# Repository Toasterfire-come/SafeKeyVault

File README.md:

# SafeKeyVault

This project is designed to be a copmplete and total alternative to managed password holders. Including features  like one click copy for authenticators which allows the same access as a microsoft auth, but with more controll. Additionaly features like autofill, and hardware key capabilities are all wrapped in the same authenticator. There is one universal settings and interface (HTML) to allow for any device with a browser to open and use passwords. This board was desiged as complete alternative to web extentions or websites having a data breach and you loosing all of your passwords. Features to prevent this are the Phishing noteices where when you attempt to fill in your password or use the device on a site like G00gle.com instead of google.com, a popup will appear informing you of a potential scam. As well as autogenerated secure passwords, week password indicators, and very good cryptography. This device uses a locked to pin system and ATECC608A binding points. With more updates to come. I built this project because I was tired of Google asking me to save every password and wanted a local opensource alternitive that does it all.

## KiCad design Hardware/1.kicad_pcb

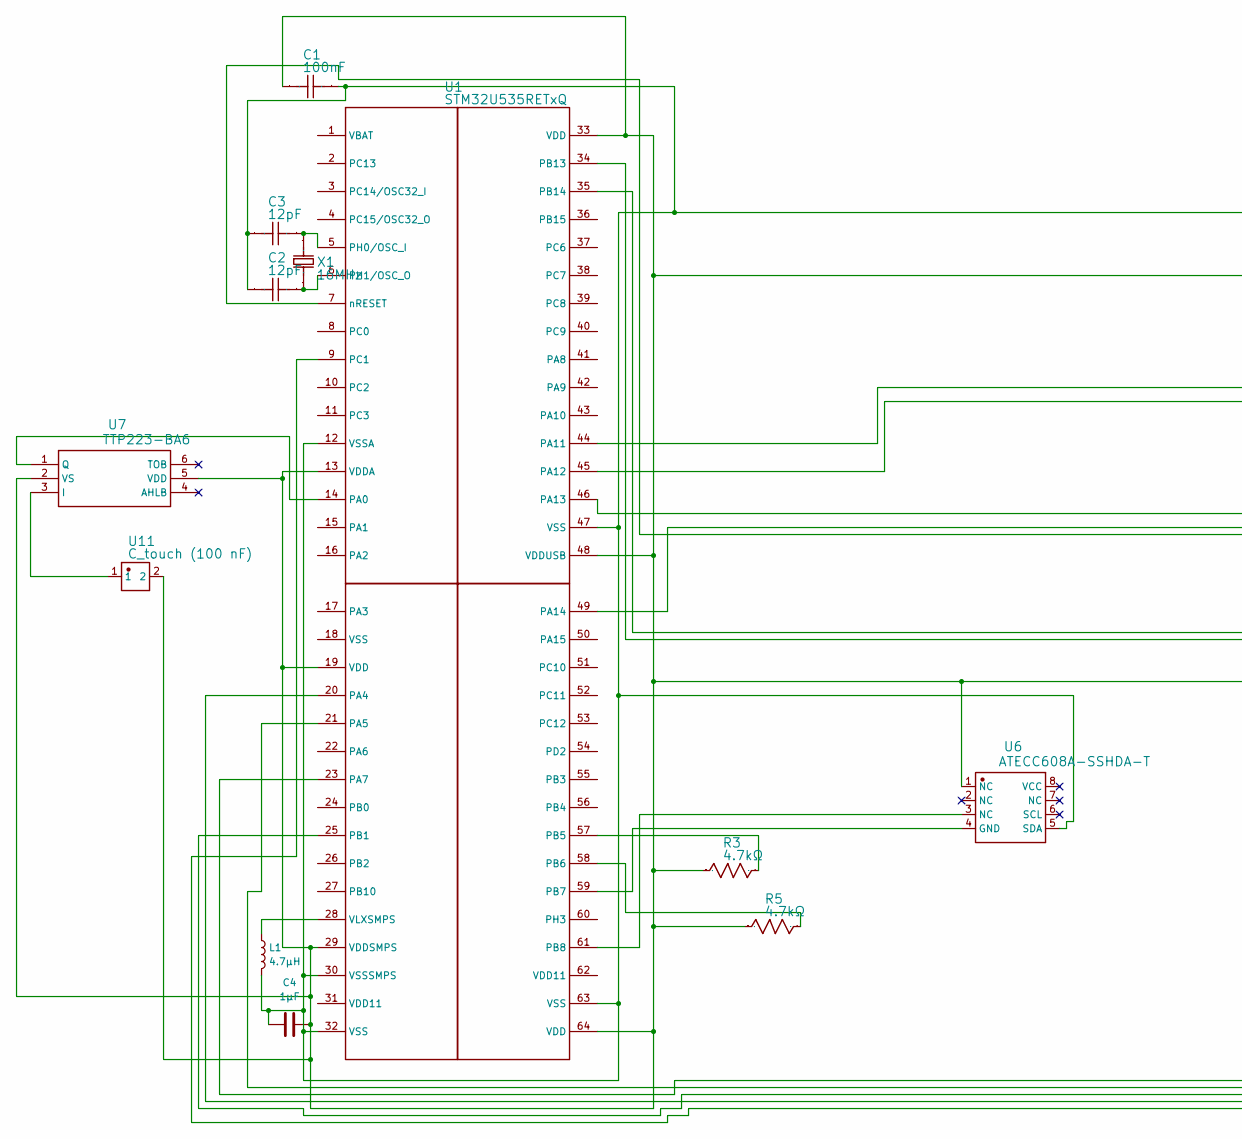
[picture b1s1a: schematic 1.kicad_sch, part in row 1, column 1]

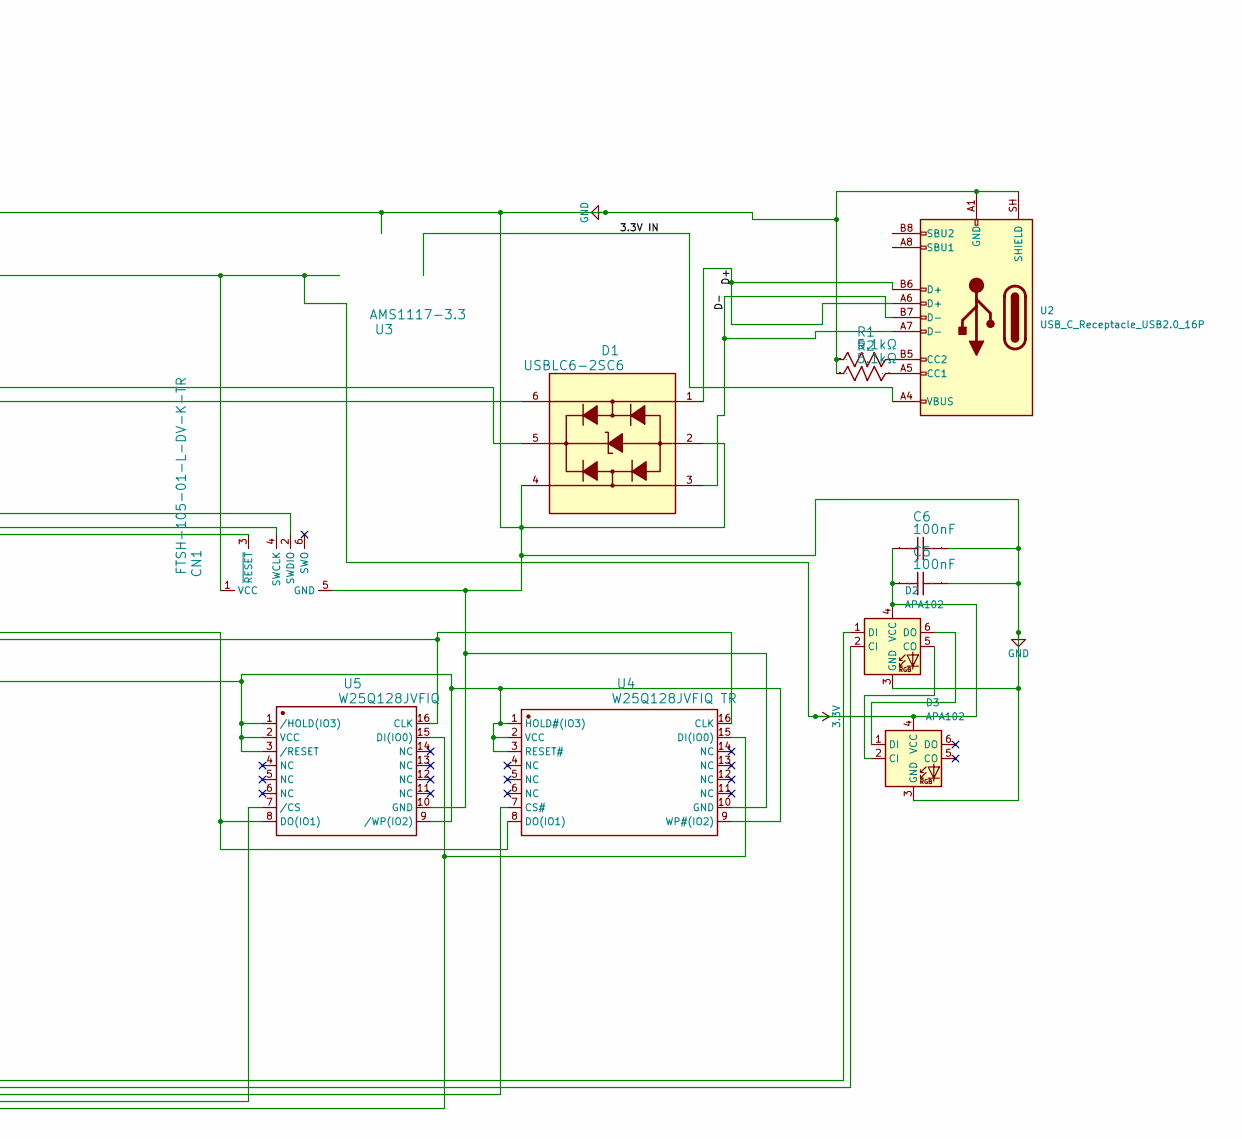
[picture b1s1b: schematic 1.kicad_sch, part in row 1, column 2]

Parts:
C1, C5, C6: 100nF; C_0603_1608Metric
C2, C3: 12pF; C_0603_1608Metric
C4: 1µF; C_0603_1608Metric
CN1: FTSH-105-01-L-DV-K-TR; Tag-Connect_TC2030-IDC-NL_2x03_P1.27mm_Vertical; Manufacturer Part FTSH-105-01-L-DV-K-TR
D1: USBLC6-2SC6; SOT-23-6; Manufacturer Part USBLC6-2SC6
D2, D3: APA102; LED-APA102-2020
L1: 4.7µH; L_0603_1608Metric
R1, R2: 5.1kΩ; R_0603_1608Metric
R3, R5: 4.7kΩ; R_0603_1608Metric
U1: STM32U535RETxQ; LQFP-64_10x10mm_P0.5mm
U2: USB_C_Receptacle_USB2.0_16P; USB_C_Receptacle_GCT_USB4105-xx-A_16P_TopMnt_Horizontal
U3: AMS1117-3.3; SOT-223-3_TabPin2; Manufacturer Part AMS1117-3.3
U4: W25Q128JVFIQ TR; SOIC-16_3.9x9.9mm_P1.27mm; Manufacturer Part W25Q128JVFIQ TR
U5: W25Q128JVFIQ; SOIC-16_3.9x9.9mm_P1.27mm; Manufacturer Part W25Q128JVFIQ
U6: ATECC608A-SSHDA-T; SOT-23-8; Manufacturer Part ATECC608A-SSHDA-T
U7: TTP223-BA6; SOT-23-6; Manufacturer Part TTP223-BA6
U11: C_touch (100 nF); C_0603_1608Metric; Manufacturer Part TOUCH
X1: 16MHz; Crystal_SMD_3225-4Pin_3.2x2.5mm; Manufacturer Part NX3225GB-16MHZ-STD-CRA-2

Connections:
3.3V: C1.1, C4.1, C5.1, C6.1, CN1.1 (VCC), D2.4 (VCC), D3.4 (VCC), R3.1, R5.1, U1.13 (VDDA), U1.19 (VDD), U1.29 (VDDSMPS), U1.33 (VDD), U1.48 (VDDUSB), U1.64 (VDD), U3.2 (VO), U4.1 (HOLD#(IO3)), U4.2 (VCC), U4.3 (RESET#), U4.9 (WP#(IO2)), U5.1 (/HOLD(IO3)), U5.2 (VCC), U5.3 (/RESET), U5.9 (/WP(IO2)), U6.1 (NC), U7.2 (VS), U7.5 (VDD), U11.2; also elsewhere on the board
/3.3V IN: U3.3 (VI); also elsewhere on the board
/D+: D1.1, U2.A6 (D+), U2.B6 (D+); also elsewhere on the board
/D-: D1.3, U2.A7 (D-), U2.B7 (D-); also elsewhere on the board
GND: C1.2, C2.1, C3.1, C4.2, C5.2, C6.2, CN1.5 (GND), D1.2, D1.4, D2.3 (GND), D3.3 (GND), L1.2, R1.1, R2.1, U1.12 (VSSA), U1.30 (VSSSMPS), U1.32 (VSS), U1.47 (VSS), U1.63 (VSS), U2.A1 (GND), U2.A12 (GND), U2.B1 (GND), U2.B12 (GND), U2.SH (SHIELD), U3.1 (GND), U4.10 (GND), U5.10 (GND), U6.5 (SDA); also elsewhere on the board
unnamed 5: CN1.4 (SWCLK), U1.49 (PA14); also elsewhere on the board
unnamed 6: CN1.2 (SWDIO), U1.46 (PA13); also elsewhere on the board
unnamed 7: CN1.3 (~RESET), U1.7 (nRESET); also elsewhere on the board
unnamed 8: D2.2 (CI), U1.21 (PA5); also elsewhere on the board
unnamed: D2.5 (CO), D3.2 (CI)
unnamed 10: D2.1 (DI), U1.23 (PA7); also elsewhere on the board
unnamed: D2.6 (DO), D3.1 (DI)
unnamed 12: R2.2, U2.A5 (CC1); also elsewhere on the board
unnamed 13: R1.2, U2.B5 (CC2); also elsewhere on the board
unnamed 14: U1.14 (PA0), U7.1 (Q); also elsewhere on the board
unnamed 15: U1.20 (PA4), U5.7 (/CS); also elsewhere on the board
unnamed 16: D1.5, U1.44 (PA11); also elsewhere on the board
unnamed 17: D1.6, U1.45 (PA12); also elsewhere on the board
unnamed 18: U1.25 (PB1), U4.7 (CS#); also elsewhere on the board
unnamed 19: R3.2, U1.57 (PB5); also elsewhere on the board
unnamed 20: R5.2, U1.58 (PB6); also elsewhere on the board
unnamed 21: U1.59 (PB7), U6.4 (GND); also elsewhere on the board
unnamed 22: U1.61 (PB8), U6.3 (NC); also elsewhere on the board
unnamed 23: U1.34 (PB13), U4.16 (CLK), U5.16 (CLK); also elsewhere on the board
unnamed 24: U1.35 (PB14), U4.8 (DO(IO1)), U5.8 (DO(IO1)); also elsewhere on the board
unnamed 25: U1.9 (PC1), U4.15 (DI(IO0)), U5.15 (DI(IO0)); also elsewhere on the board
unnamed 26: C3.2, U1.5 (PH0/OSC_I), X1.2; also elsewhere on the board
unnamed 27: C2.2, U1.6 (PH1/OSC_O), X1.1; also elsewhere on the board
unnamed 28: L1.1, U1.28 (VLXSMPS); also elsewhere on the board
unnamed: U2.A4 (VBUS), U2.A9 (VBUS), U2.B4 (VBUS), U2.B9 (VBUS)
unnamed: U7.3 (I), U11.1

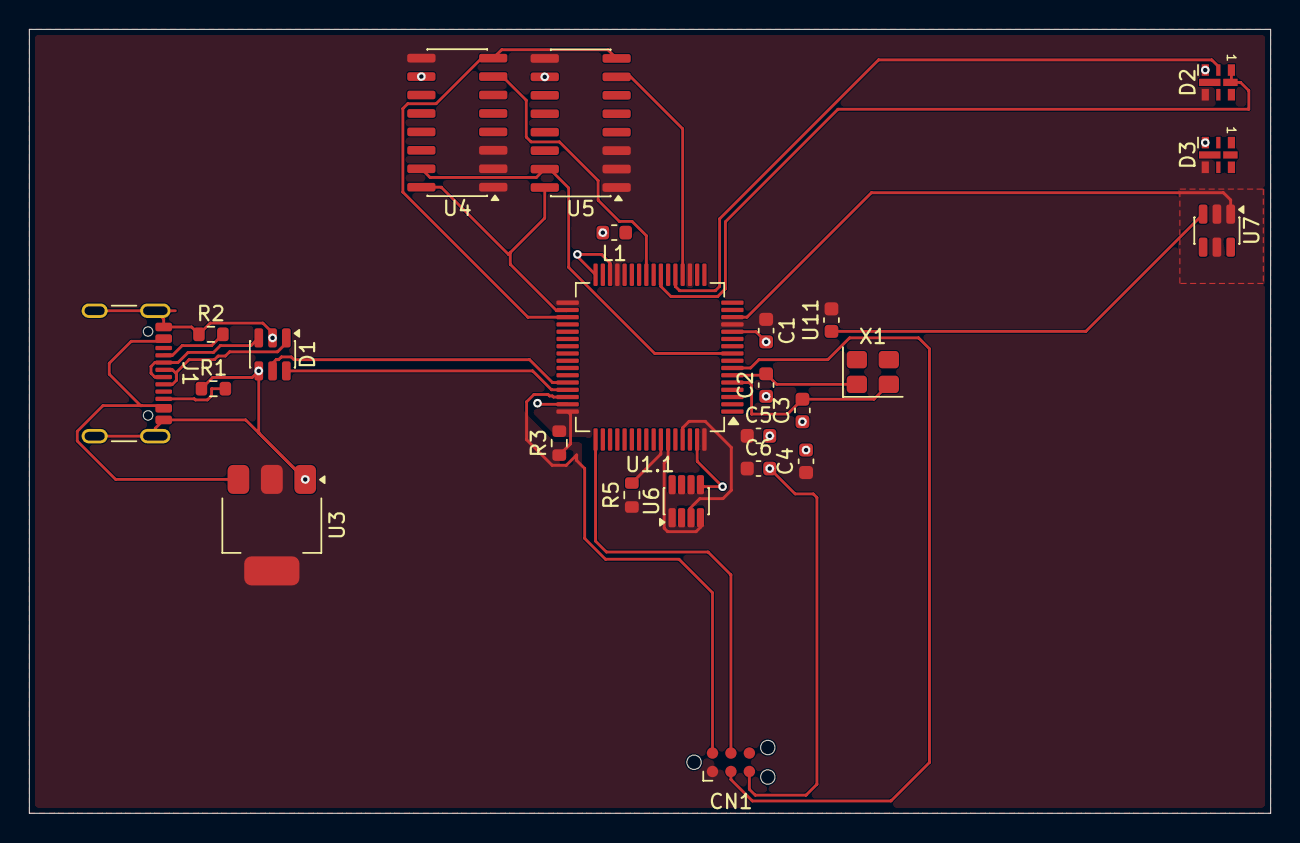
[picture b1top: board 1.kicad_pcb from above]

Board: 2 copper layers, 85.5 x 54.0 mm, 24 parts (0 on the bottom side), 30 nets.

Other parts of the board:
J1: USB_C_Receptacle_USB2.0_16P; USB_C_Receptacle_GCT_USB4105-xx-A_16P_TopMnt_Horizontal
U1.1: STM32U535RETxQ; LQFP-64_10x10mm_P0.5mm

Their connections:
3.3V: U1.1.13 (VDDA), U1.1.19 (VDD), U1.1.29 (VDDSMPS), U1.1.33 (VDD), U1.1.48 (VDDUSB), U1.1.64 (VDD); also elsewhere on the board
/3.3V IN: J1.A4 (VBUS), J1.A9 (VBUS), J1.B4 (VBUS), J1.B9 (VBUS); also elsewhere on the board
/D+: J1.A6 (D+), J1.B6 (D+); also elsewhere on the board
/D-: J1.A7 (D-), J1.B7 (D-); also elsewhere on the board
GND: J1.A1 (GND), J1.A12 (GND), J1.B1 (GND), J1.B12 (GND), J1.SH (SHIELD), U1.1.12 (VSSA), U1.1.30 (VSSSMPS), U1.1.32 (VSS), U1.1.47 (VSS), U1.1.63 (VSS); also elsewhere on the board
unnamed 5: U1.1.49 (PA14); also elsewhere on the board
unnamed 6: U1.1.46 (PA13); also elsewhere on the board
unnamed 7: U1.1.7 (nRESET); also elsewhere on the board
unnamed 8: U1.1.21 (PA5); also elsewhere on the board
unnamed 10: U1.1.23 (PA7); also elsewhere on the board
unnamed 12: J1.A5 (CC1); also elsewhere on the board
unnamed 13: J1.B5 (CC2); also elsewhere on the board
unnamed 14: U1.1.14 (PA0); also elsewhere on the board
unnamed 15: U1.1.20 (PA4); also elsewhere on the board
unnamed 16: U1.1.44 (PA11); also elsewhere on the board
unnamed 17: U1.1.45 (PA12); also elsewhere on the board
unnamed 18: U1.1.25 (PB1); also elsewhere on the board
unnamed 19: U1.1.57 (PB5); also elsewhere on the board
unnamed 20: U1.1.58 (PB6); also elsewhere on the board
unnamed 21: U1.1.59 (PB7); also elsewhere on the board
unnamed 22: U1.1.61 (PB8); also elsewhere on the board
unnamed 23: U1.1.34 (PB13); also elsewhere on the board
unnamed 24: U1.1.35 (PB14); also elsewhere on the board
unnamed 25: U1.1.9 (PC1); also elsewhere on the board
unnamed 26: U1.1.5 (PH0/OSC_I); also elsewhere on the board
unnamed 27: U1.1.6 (PH1/OSC_O); also elsewhere on the board
unnamed 28: U1.1.28 (VLXSMPS); also elsewhere on the board

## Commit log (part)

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2026-04-07 Add SVJ generator with RP2040 pin mapping
2026-04-07 Generate RP2040 board SVJ and ERC report
2026-04-07 Fix USB series resistors and complete RP2040 QSPI boot flash
2026-04-07 Add custom firmware scaffold with security policy
2026-04-07 Fix touch-gated fill test flow
2026-04-07 Ignore firmware build artifacts
2026-04-07 Implement action engine with touch-confirmed workflows
2026-04-07 Add lockout/wipe controls and popup behavior settings
2026-04-07 Add UI feedback mapping and manual popup arm flow
2026-04-08 Add security hardening modules, docs, and browser extension
2026-04-08 Add nonce replay guard, PIN change flow, and extension UI wiring
2026-04-08 Fix C99 compatibility includes for protocol and state machine
2026-04-08 Harden browser command inputs and align protocol docs
2026-04-08 Tighten browser field checks and stabilize protocol tests
2026-04-08 Pivot to device-only plug-and-play workflow
2026-04-08 Fix device-only API header and stabilize device flow tests
2026-04-08 Enforce single-press fill and hold-for-settings model
2026-04-08 Declare button press/hold APIs in action engine header
2026-04-08 Fallback single press to settings when context is unknown
2026-04-08 Add actionable settings popup operations and tests
2026-04-08 Wire settings popup actions and enforce one-press/hold interaction mode
2026-04-08 Add crypto engine abstraction with AEAD/KDF interfaces
2026-04-08 Fix AEAD interface signatures and crypto engine tests
2026-04-08 Encrypt settings persistence and add tamper checks
2026-04-08 Expose settings store tamper test snapshot/restore hooks
2026-04-08 Add versioned password envelope and crypto roundtrip tests
2026-04-08 Add storage, secure boot, session, FIDO2, and HAL scaffolds
2026-04-08 Stabilize security scaffolds and add integration coverage
2026-04-09 Add production build mode and release folder assets
2026-04-09 Migrate project naming and board spec to STM32U5
2026-04-11 initial
2026-04-19 Create a
2026-04-19 Revise README for STM32U5 Password Holder
    Updated project description to clarify features and purpose.
2026-04-19 feat: Add stm32u5xx_hal.h header file
